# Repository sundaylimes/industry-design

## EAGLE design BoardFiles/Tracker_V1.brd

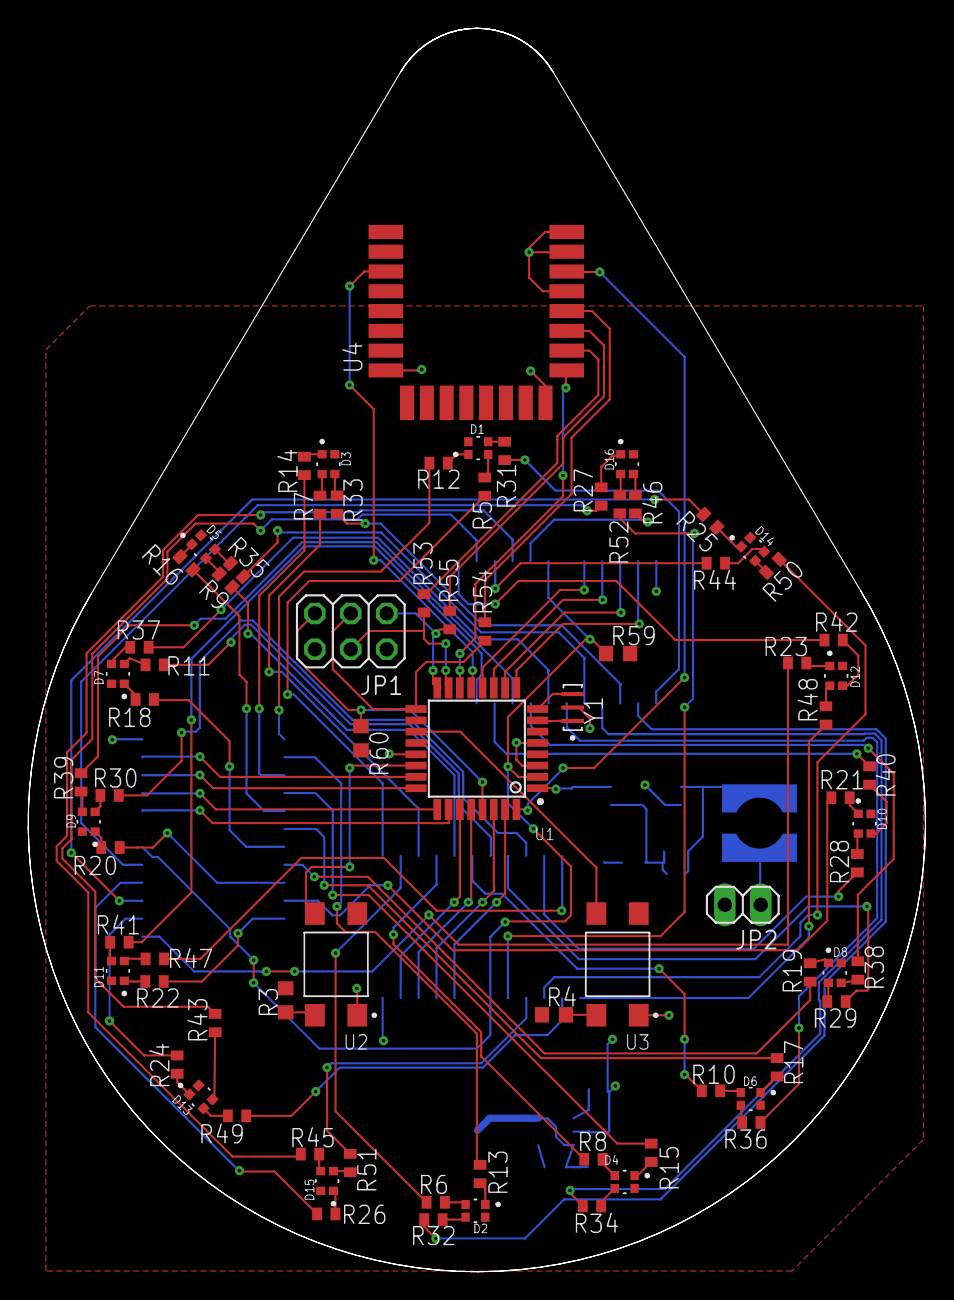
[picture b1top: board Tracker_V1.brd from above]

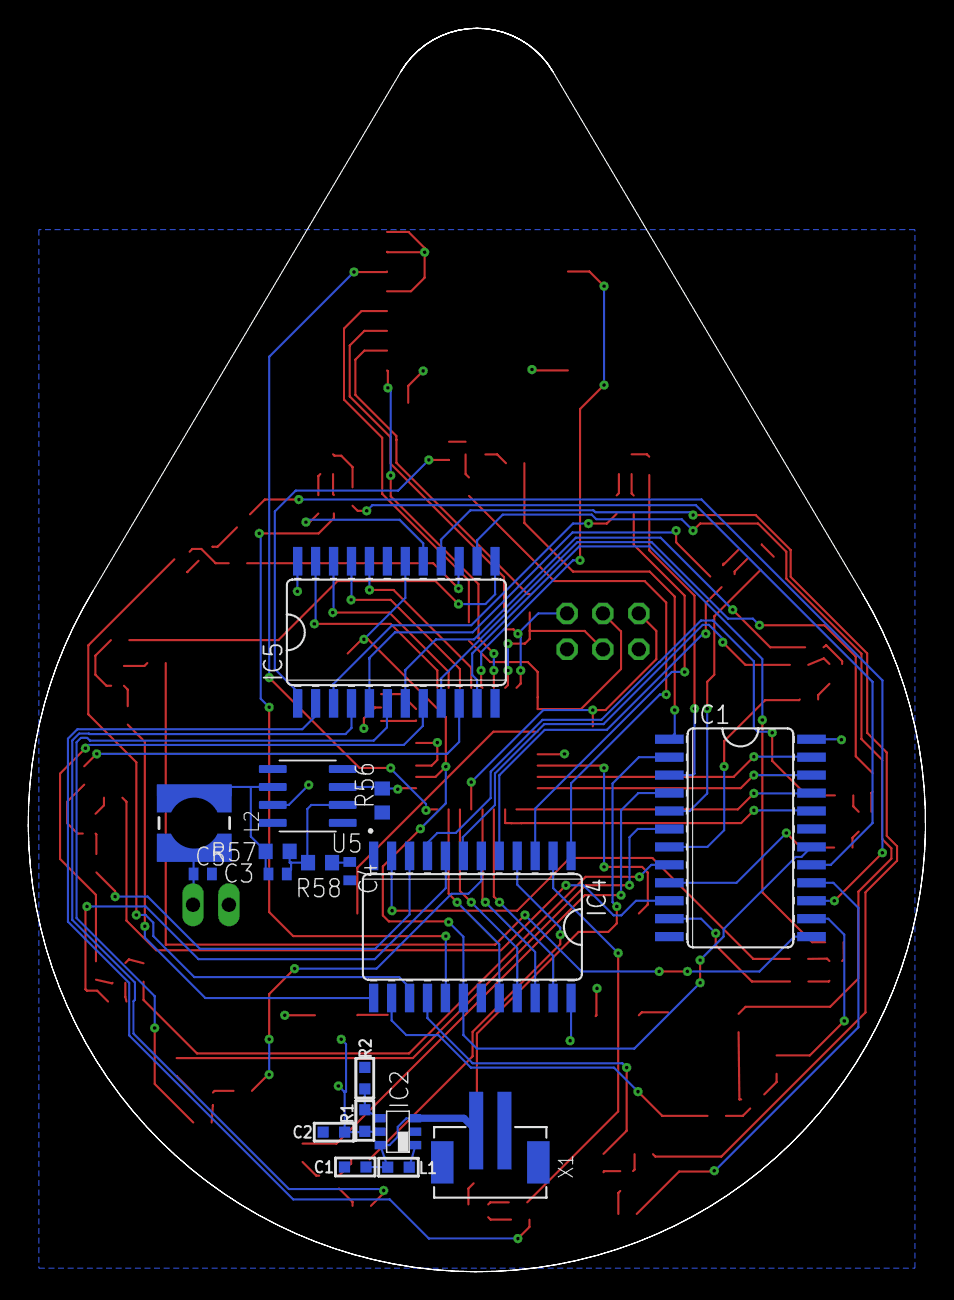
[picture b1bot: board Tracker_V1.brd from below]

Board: 2 copper layers, 63.5 x 88.0 mm, 96 parts (18 on the bottom side), 135 nets.

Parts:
C1, C2: 10u; C0603
C3: 47pF; C0402
C4: 1uF; C0402
C5: 4.7uF; C0402
D1, D2, D3, D4, D5, D6, D7, D8, D9, D10, D11, D12, D13, D14, D15, D16: LED_EAST1616RGBA3
IC1, IC4, IC5: 74154DW; SO24W
IC2: TPS61070DDC; TSOT23-6_DDC
JP1: 2X03
JP2: 1X02
L1: 4.7u; L0603
L2: 1500uH; WE-TPC_4828
R1, R56: 1M; R0603
R2: 178k; R0603
R3, R4, R58, R59, R60: 10k; R0603
R5, R6, R7, R8, R9, R10, R11, R12, R13, R14, R15, R16, R17, R18, R19, R20, R21, R22, R23, R24, R25, R26, R27, R28, R29, R30, R31, R32, R33, R34, R35, R36, R37, R38, R39, R40, R41, R42, R43, R44, R45, R46, R47, R48, R49, R50, R51, R52: 750 1%; R0402
R53, R54, R55: 0; R0402
R57: 220k; R0603
U1: ATMEGA328P-AU; QFP80P900X900X120-32N
U2, U3: TL3305AF260QG; SW_TL3305AF260QG
U4: DWM1000; XCVR_DWM1000
U5: UA741CD; SOIC127P600X175-8N
X1: B2B-PH-SM4-TB
Y1: CSTCE16M0V53-R0; OSC_CSTCE16M0V53-R0

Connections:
BL_A: IC1.23, U1.23
BL_B: IC1.22, U1.24
BL_C: IC1.21, U1.25
BL_D: IC1.20, U1.26
GND: C1.1, C2.1, C4.2, C5.2, IC1.12, IC1.19, IC2.2, IC4.12, IC4.19, IC5.12, IC5.19, JP1.6, JP2.2, R2.1, R56.1, U1.3, U1.5, U1.21, U2.1, U3.1, U4.8, U4.16, U4.21, U4.23, U4.24, U5.4, X1.1, Y1.2
GR_A: IC4.23, U1.27
GR_B: IC4.22, U1.28
GR_C: IC4.21, U1.30
GR_D: IC4.20, U1.31
LED_ON: IC1.18, IC4.18, IC5.18, R59.1, U1.2
unnamed: IC2.1, L1.1
unnamed: C1.2, IC2.3, IC2.6, L1.2, X1.2
unnamed: R4.2, U3.3
unnamed: D1.1, R12.2
unnamed: R3.2, U2.3
unnamed: IC2.4, R1.1, R2.2
unnamed: D7.1, R18.2
unnamed: D3.1, R14.2
unnamed: D4.1, R15.2
unnamed: D5.1, R16.2
unnamed: D6.1, R17.2
unnamed: D2.1, R13.2
unnamed: D8.1, R19.2
unnamed: D9.1, R20.2
unnamed: D10.1, R21.2
unnamed: D11.1, R22.2
unnamed: D12.1, R23.2
unnamed: D13.1, R24.2
unnamed: D14.1, R25.2
unnamed: D15.1, R26.2
unnamed: D16.1, R27.2
unnamed: IC4.1, R5.1
unnamed: IC4.2, R6.1
unnamed: IC4.3, R7.1
unnamed: D4.2, R8.2
unnamed: D5.2, R9.2
unnamed: D7.2, R11.2
unnamed: D6.2, R10.2
unnamed: D8.2, R29.2
unnamed: D9.2, R30.2
unnamed: IC4.10, R28.1
unnamed: D11.2, R47.2
unnamed: D12.2, R48.2
unnamed: IC4.14, R49.1
unnamed: IC4.15, R50.1
unnamed: IC4.16, R51.1
unnamed: IC4.17, R52.1
unnamed: D16.4, R46.2
unnamed: D15.4, R45.2
unnamed: D14.4, R44.2
unnamed: D13.4, R43.2
unnamed: D12.4, R42.2
unnamed: D11.4, R41.2
unnamed: D10.4, R40.2
unnamed: D9.4, R39.2
unnamed: D8.4, R38.2
unnamed: D7.4, R37.2
unnamed: D6.4, R36.2
unnamed: D5.4, R35.2
unnamed: D4.4, R34.2
unnamed: D3.4, R33.2
unnamed: D2.4, R32.2
unnamed: D1.4, R31.2
unnamed: D1.2, R5.2
unnamed: D2.2, R6.2
unnamed: D3.2, R7.2
unnamed: IC4.4, R8.1
unnamed: IC4.5, R9.1
unnamed: IC4.6, R10.1
unnamed: IC4.7, R11.1
unnamed: IC1.1, R12.1
unnamed: IC1.2, R13.1
unnamed: IC1.3, R14.1
unnamed: IC1.4, R15.1
unnamed: IC1.5, R16.1
unnamed: IC1.6, R17.1
unnamed: IC1.7, R18.1
unnamed: IC1.8, R19.1
unnamed: IC1.9, R20.1
unnamed: IC1.10, R21.1
unnamed: IC1.11, R22.1
unnamed: IC1.13, R23.1
unnamed: IC1.14, R24.1
unnamed: IC1.15, R25.1
unnamed: IC1.16, R26.1
unnamed: IC1.17, R27.1
unnamed: IC4.8, R29.1
unnamed: IC4.9, R30.1
unnamed: D10.2, R28.2
unnamed: IC5.1, R31.1
unnamed: IC5.2, R32.1
unnamed: IC5.3, R33.1
unnamed: IC5.4, R34.1
unnamed: IC5.5, R35.1
unnamed: IC5.6, R36.1
unnamed: IC5.7, R37.1
unnamed: IC5.8, R38.1
unnamed: IC5.9, R39.1
unnamed: IC5.10, R40.1
unnamed: IC5.11, R41.1
unnamed: IC5.13, R42.1
unnamed: IC5.14, R43.1
unnamed: IC5.15, R44.1
unnamed: IC5.16, R45.1
unnamed: IC5.17, R46.1
unnamed: IC4.11, R47.1
unnamed: IC4.13, R48.1
unnamed: D13.2, R49.2
unnamed: D14.2, R50.2
unnamed: D15.2, R51.2
unnamed: D16.2, R52.2
unnamed: U1.14, U4.17
unnamed: JP1.4, R53.1, U1.15
unnamed: JP1.1, R55.1, U1.16
unnamed: JP1.3, R54.1, U1.17
unnamed: U1.13, U4.3
unnamed: U1.32, U4.22
unnamed: U1.8, Y1.3
unnamed: U1.7, Y1.1
unnamed: JP1.5, R60.1, U1.29
unnamed: R53.2, U4.18
unnamed: R54.2, U4.20
unnamed: R55.2, U4.19
unnamed: R56.2, U1.1, U5.3
unnamed: C3.1, L2.1, R57.1, U5.6
unnamed: C5.1, JP2.1, L2.2
unnamed: C3.2, R57.2, R58.2, U5.2
unnamed: C4.1, R58.1
RD_A: IC5.23, U1.9
RD_B: IC5.22, U1.10
RD_C: IC5.21, U1.11
RD_D: IC5.20, U1.12
SW1: U1.19, U3.4
SW2: U1.22, U2.4
VCC: C2.2, D1.3, D2.3, D3.3, D4.3, D5.3, D6.3, D7.3, D8.3, D9.3, D10.3, D11.3, D12.3, D13.3, D14.3, D15.3, D16.3, IC1.24, IC2.5, IC4.24, IC5.24, JP1.2, R1.2, R3.1, R4.1, R59.2, R60.2, U1.4, U1.6, U1.18, U1.20, U4.5, U4.6, U4.7, U5.7

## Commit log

2020-11-02 schematic
2020-11-07 this is a test.
2020-11-07 this a test
2020-11-07 Added folders and backlogged documents.
2020-11-07 check boos
2020-11-08 pushing the code right into the repo
2020-11-09 Ltspice schematics for generater speaker signals
2020-11-09 fixed test stuff
2020-11-09 Added tracker schematic
2020-11-09 fixed folder formating for linux
2020-11-09 removed spaces from folders
2020-11-09 schematics and code
2020-11-09 fixed spelling and removed code folder
2020-11-12 wiki
2020-11-12 removed wiki
2020-11-13 Final speaker driver circuit completed
2020-11-14 Added Gantt chart.
2020-11-14 cleaned up files
2020-11-14 Merging with main branch.
2020-11-14 Adding v3 of tracker schematic.
2020-11-15 Nov 14th schematic
2020-12-06 board files added.
2020-12-09 Added backlogged final schematic file.

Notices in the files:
parts and their libraries:
rc-master-smd: Copyright (C) 2007, Bob Starr
Eagle_WE-TPC_rev19a: Copyright: Würth Elektronik
